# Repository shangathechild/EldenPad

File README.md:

# EldenPad
Hello! This is my custom macropad for hackclub x amd Blueprint 
## Description
- This thing is chonky massive(i couldnt fit my wires and my engravings on a small one)
- I have a 0.91 inch OLED display displaying a hollow knight image, im gonna animate it and put a clock on it later on

- I got 6 LEDs with RGB
- I have a rotary encoder which controls my volume
- I have 9 keys (including the rotary encoder switch)
- I have a malenia and alaxander engraving on it :)
- I have two custom keycaps, one being the sekiro death symbol and the elden ring logo.
## PCB
**schematic**

Even though it says MINI LEDs the, footprint is mini E

**pcb**

The wires look super messy, this is my first time and idk how to make it cleaner.

## CAD

This was the most fun part of the entire process, even though it was painful. I used the education version of autodesk fusion for all this.

## Firmware

This was by far the HARDEST part of the entire process as it was really confusing ( ive never writen code in C before so i had to learn everthing from GfG, and i took a little bit of help from gemini cuz i didnt understand what to write in the config and stuff for QMK)

I wrote my firmware in QMK and you can find it in the REPO, the fully compiled one in the Production section

## BOM
- 1 Seeed XIAO RP2040
- 8x MX-Style switches
- 6x SK6812 MINI - E LEDs
- 9x through-hole 1N4148 Diodes
- 1 SSD1306 128*32
- 4x M3x16mm screws
- 4x M3x5mx4mm heatset inserts

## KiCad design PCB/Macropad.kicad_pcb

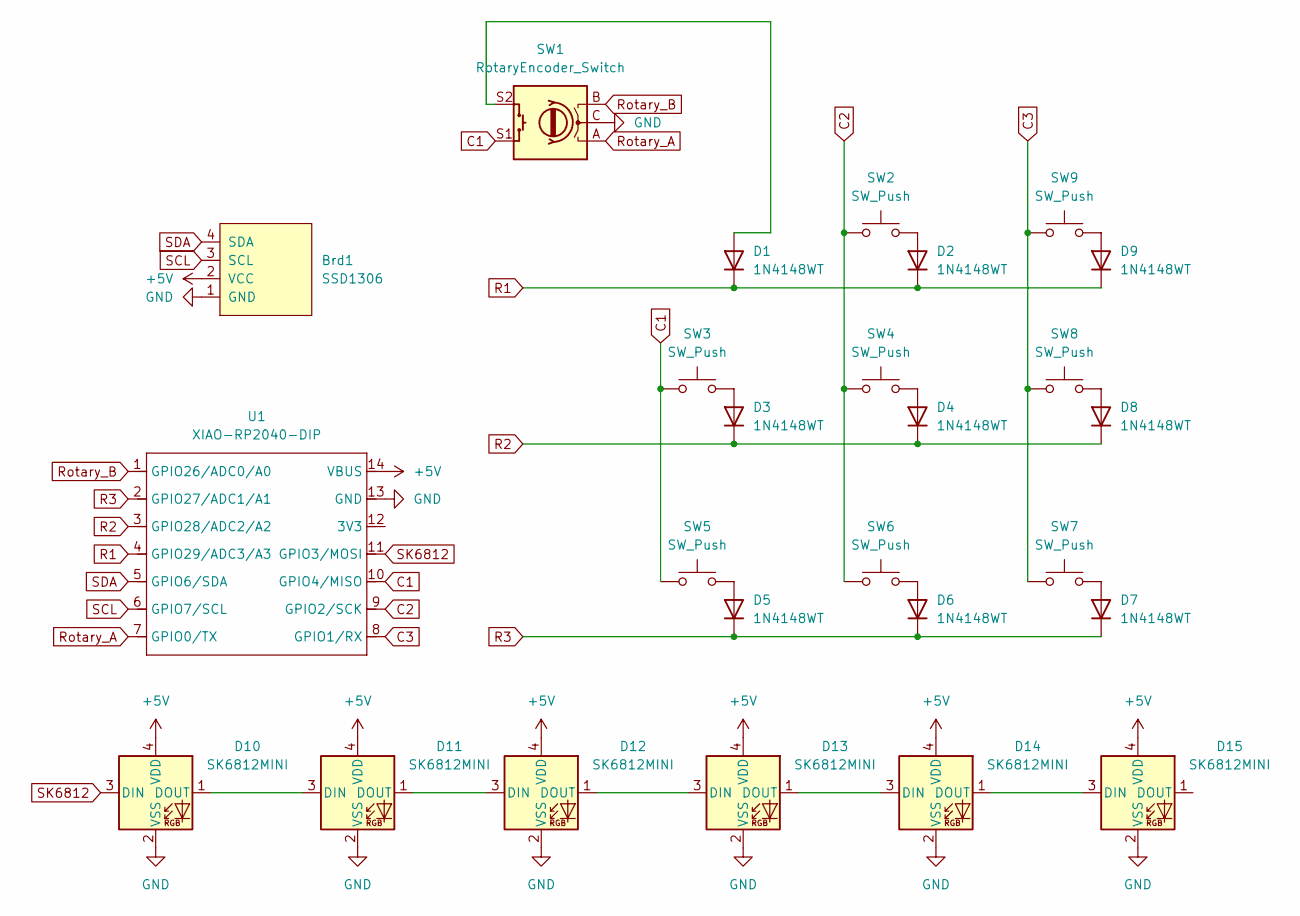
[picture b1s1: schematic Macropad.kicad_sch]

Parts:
Brd1: SSD1306; SSD1306-0.91-OLED-4pin-128x32
D1, D2, D3, D4, D5, D6, D7, D8, D9: 1N4148WT; D_DO-35_SOD27_P7.62mm_Horizontal
D10, D11, D12, D13, D14, D15: SK6812MINI; SK6812MINI-E_fixed
SW1: RotaryEncoder_Switch; RotaryEncoder_Alps_EC11E-Switch_Vertical_H20mm
SW2, SW3, SW4, SW5, SW6, SW7, SW8, SW9: SW_Push; SW_Cherry_MX_1.00u_PCB
U1: XIAO-RP2040-DIP; Seeed_XIAO_RP2040

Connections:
+5V: Brd1.2 (VCC), D10.4 (VDD), D11.4 (VDD), D12.4 (VDD), D13.4 (VDD), D14.4 (VDD), D15.4 (VDD), U1.14 (VBUS)
C1: SW1.S1, SW3.1, SW5.1, U1.10 (GPIO4/MISO)
C2: SW2.1, SW4.1, SW6.1, U1.9 (GPIO2/SCK)
C3: SW7.1, SW8.1, SW9.1, U1.8 (GPIO1/RX)
GND: Brd1.1 (GND), D10.2 (VSS), D11.2 (VSS), D12.2 (VSS), D13.2 (VSS), D14.2 (VSS), D15.2 (VSS), SW1.C, U1.13 (GND)
unnamed: D1.2 (A), SW1.S2
unnamed: D2.2 (A), SW2.2
unnamed: D3.2 (A), SW3.2
unnamed: D4.2 (A), SW4.2
unnamed: D5.2 (A), SW5.2
unnamed: D6.2 (A), SW6.2
unnamed: D7.2 (A), SW7.2
unnamed: D8.2 (A), SW8.2
unnamed: D9.2 (A), SW9.2
unnamed: D10.1 (DOUT), D11.3 (DIN)
unnamed: D11.1 (DOUT), D12.3 (DIN)
unnamed: D12.1 (DOUT), D13.3 (DIN)
unnamed: D13.1 (DOUT), D14.3 (DIN)
unnamed: D14.1 (DOUT), D15.3 (DIN)
R1: D1.1 (K), D2.1 (K), D9.1 (K), U1.4 (GPIO29/ADC3/A3)
R2: D3.1 (K), D4.1 (K), D8.1 (K), U1.3 (GPIO28/ADC2/A2)
R3: D5.1 (K), D6.1 (K), D7.1 (K), U1.2 (GPIO27/ADC1/A1)
Rotary_A: SW1.A, U1.7 (GPIO0/TX)
Rotary_B: SW1.B, U1.1 (GPIO26/ADC0/A0)
SCL: Brd1.3 (SCL), U1.6 (GPIO7/SCL)
SDA: Brd1.4 (SDA), U1.5 (GPIO6/SDA)
SK6812: D10.3 (DIN), U1.11 (GPIO3/MOSI)

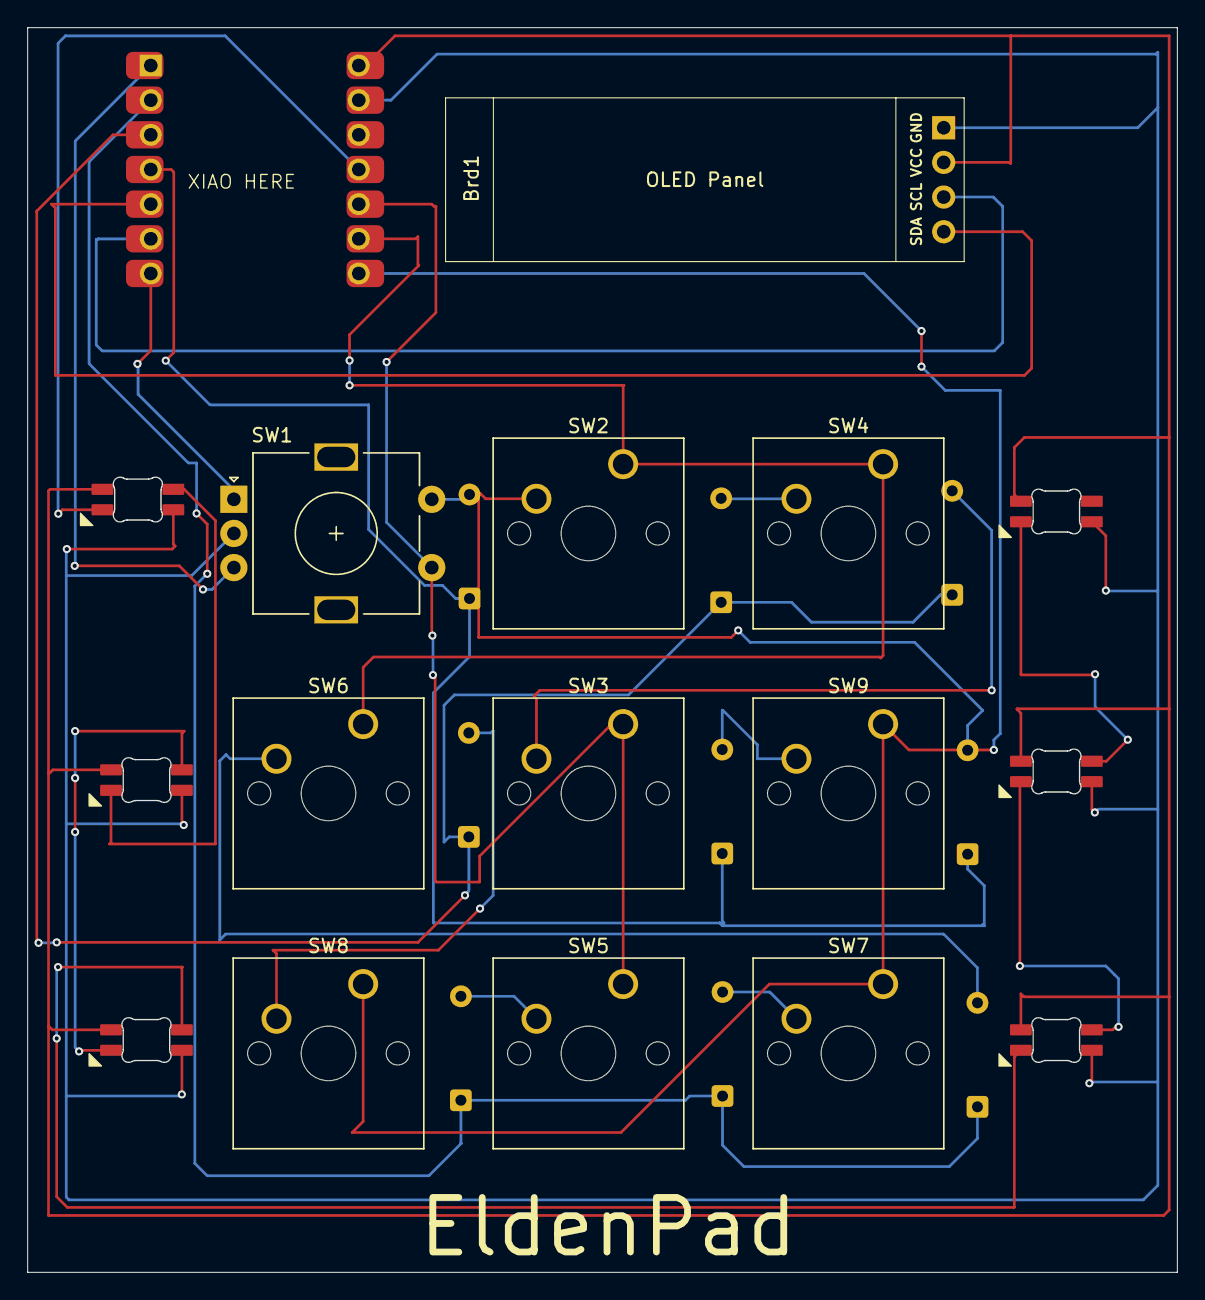
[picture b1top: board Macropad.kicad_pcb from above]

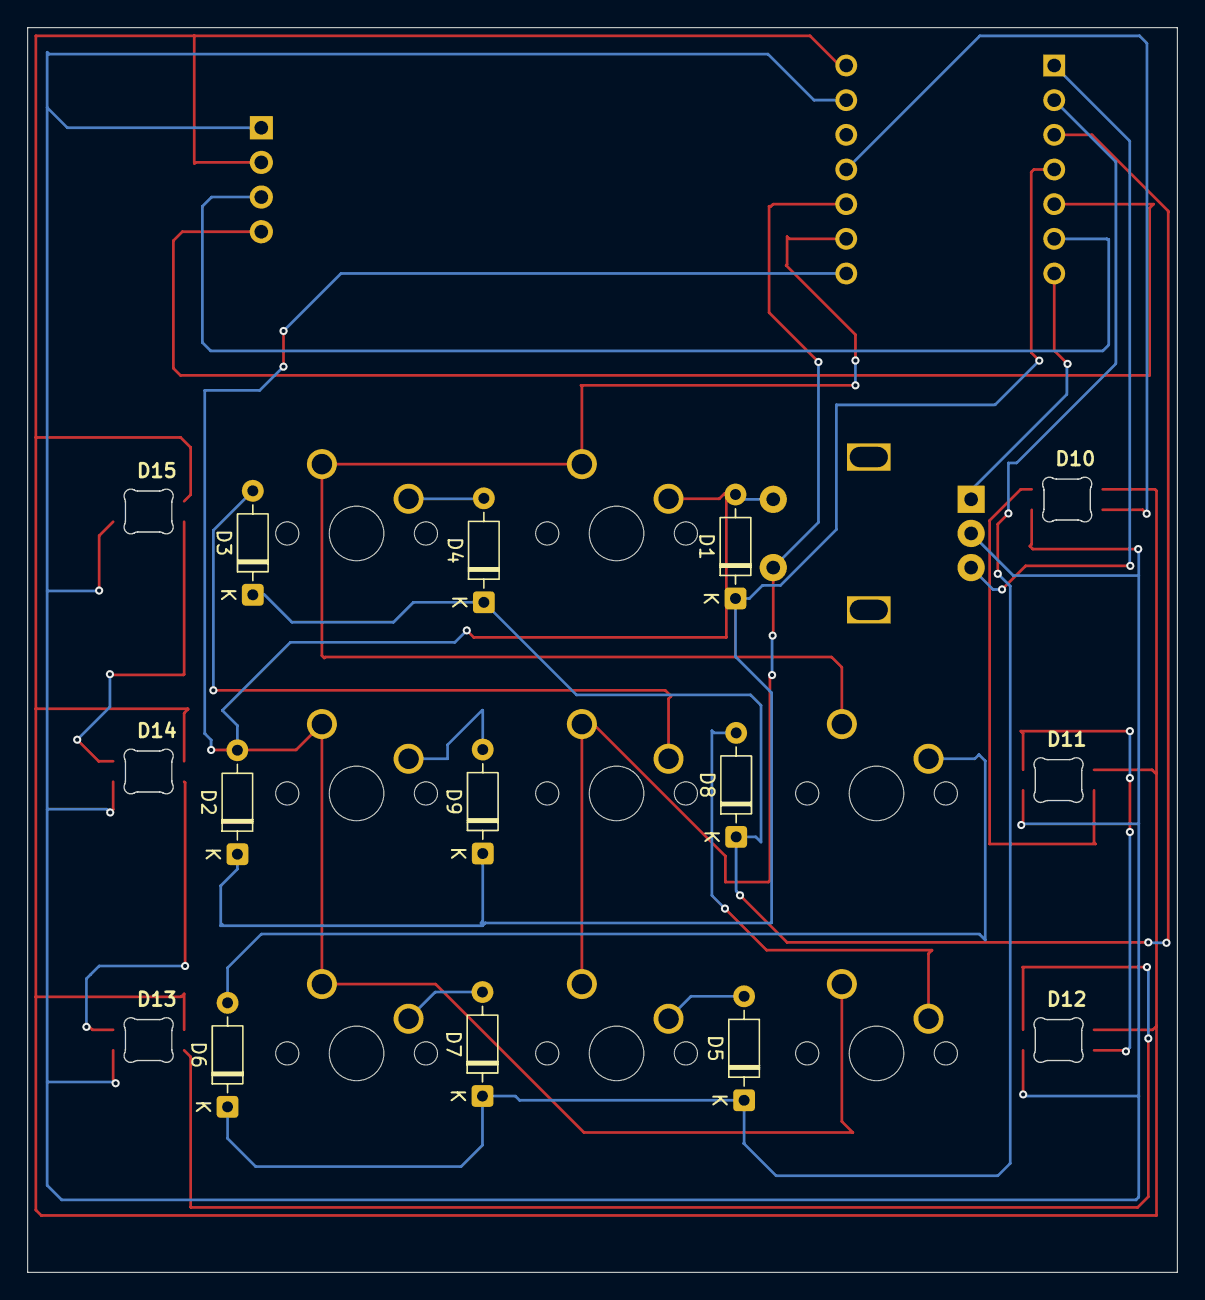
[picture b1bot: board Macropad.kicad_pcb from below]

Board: 2 copper layers, 84.2 x 91.2 mm, 26 parts (15 on the bottom side), 27 nets.

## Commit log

2026-02-15 Update README with project details and description
    Expanded project description and added details about the OLED display.
2026-02-15 Fix image link in README.md
    Updated image link formatting in README.
2026-02-15 Add image placeholder for hollow knight in README
    Updated README to include an image of the hollow knight.
2026-02-15 Fix image tag for hollow knight display
    Updated image tag for hollow knight in README.
2026-02-15 Enhance README with PCB, CAD, and Firmware details
    Added detailed sections about PCB, CAD, and Firmware, including images and BOM.
2026-02-15 Update README with schematic and PCB images
    Added images of the schematic and PCB to the README.
2026-02-15 Clarify firmware development challenges and resources
    Expanded explanation of firmware development process and assistance received.
2026-02-15 Update readme.md with untested note
    Removed existing content and added a note about untested status.
2026-02-15 Modify rgblight led_count in keyboard.json
    Updated rgblight led_count from 8 to 6.
2026-02-15 Update README with OLED display details
    Added a new line to describe the OLED display.
2026-02-15 Add hollow knight image to README
    Added an image of the hollow knight to the README.
